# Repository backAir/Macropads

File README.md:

# Macropads

## 10x10 Macropad

[10x10 macropad](10x10/README.md)

## 4x3 Cuty Pad

[4x3 Cuty pad](<4x3 cuty pad/README.md>)

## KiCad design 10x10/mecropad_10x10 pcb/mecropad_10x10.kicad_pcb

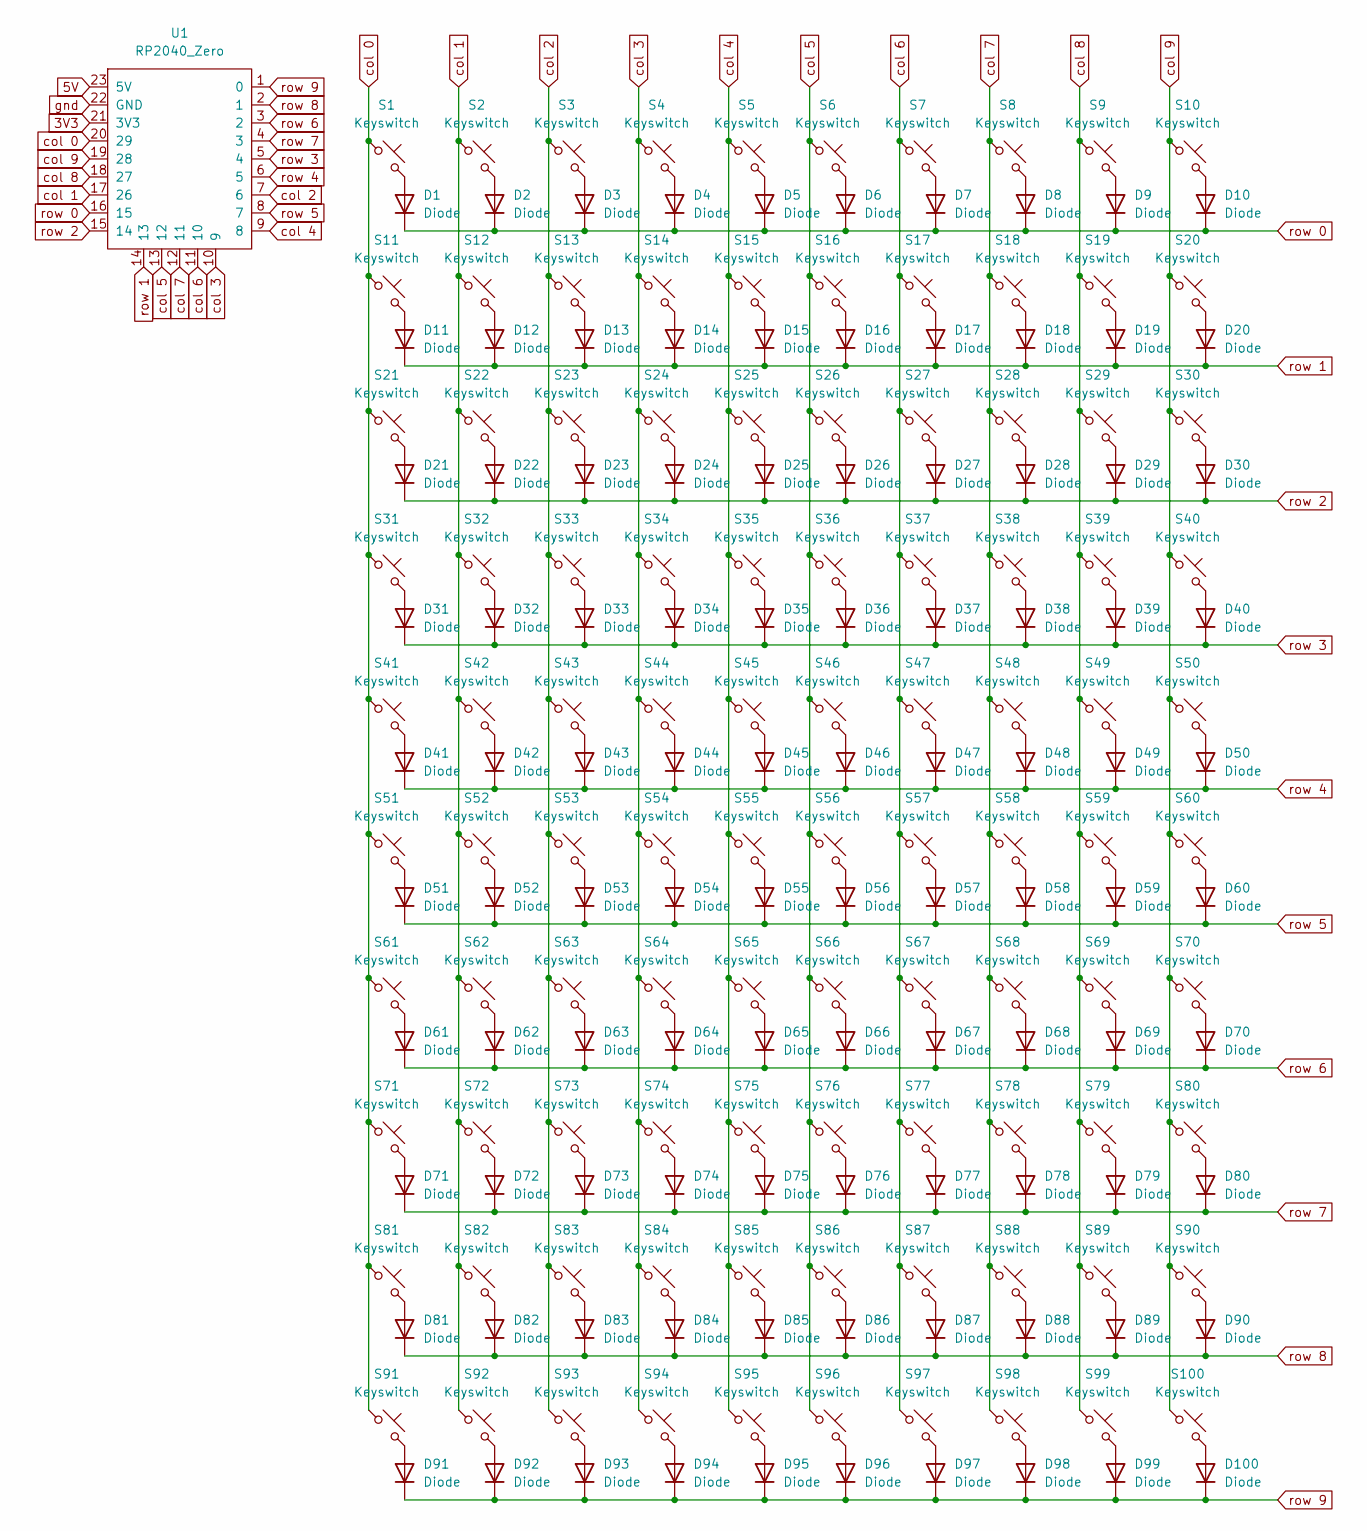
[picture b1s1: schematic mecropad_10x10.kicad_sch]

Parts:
D1, D2, D3, D4, D5, D6, D7, D8, D9, D10, D11, D12, D13, D14, D15, D16, D17, D18, D19, D20, D21, D22, D23, D24, D25, D26, D27, D28, D29, D30, D31, D32, D33, D34, D35, D36, D37, D38, D39, D40, D41, D42, D43, D44, D45, D46, D47, D48, D49, D50, D51, D52, D53, D54, D55, D56, D57, D58, D59, D60, D61, D62, D63, D64, D65, D66, D67, D68, D69, D70, D71, D72, D73, D74, D75, D76, D77, D78, D79, D80, D81, D82, D83, D84, D85, D86, D87, D88, D89, D90, D91, D92, D93, D94, D95, D96, D97, D98, D99, D100: Diode; Diode_DO-35_smol
S1, S2, S3, S4, S5, S6, S7, S8, S9, S10, S11, S12, S13, S14, S15, S16, S17, S18, S19, S20, S21, S22, S23, S24, S25, S26, S27, S28, S29, S30, S31, S32, S33, S34, S35, S36, S37, S38, S39, S40, S41, S42, S43, S44, S45, S46, S47, S48, S49, S50, S51, S52, S53, S54, S55, S56, S57, S58, S59, S60, S61, S62, S63, S64, S65, S66, S67, S68, S69, S70, S71, S72, S73, S74, S75, S76, S77, S78, S79, S80, S81, S82, S83, S84, S85, S86, S87, S88, S89, S90, S91, S92, S93, S94, S95, S96, S97, S98, S99, S100: Keyswitch; SW_BUTT-2
U1: RP2040_Zero; RP2040_Zero_round_pads

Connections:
3V3: U1.21 (3V3)
5V: U1.23 (5V)
unnamed: D1.2 (A), S1.2
unnamed: D2.2 (A), S2.2
unnamed: D3.2 (A), S3.2
unnamed: D4.2 (A), S4.2
unnamed: D5.2 (A), S5.2
unnamed: D6.2 (A), S6.2
unnamed: D7.2 (A), S7.2
unnamed: D8.2 (A), S8.2
unnamed: D9.2 (A), S9.2
unnamed: D10.2 (A), S10.2
unnamed: D11.2 (A), S11.2
unnamed: D12.2 (A), S12.2
unnamed: D13.2 (A), S13.2
unnamed: D14.2 (A), S14.2
unnamed: D15.2 (A), S15.2
unnamed: D16.2 (A), S16.2
unnamed: D17.2 (A), S17.2
unnamed: D18.2 (A), S18.2
unnamed: D19.2 (A), S19.2
unnamed: D20.2 (A), S20.2
unnamed: D21.2 (A), S21.2
unnamed: D22.2 (A), S22.2
unnamed: D23.2 (A), S23.2
unnamed: D24.2 (A), S24.2
unnamed: D25.2 (A), S25.2
unnamed: D26.2 (A), S26.2
unnamed: D27.2 (A), S27.2
unnamed: D28.2 (A), S28.2
unnamed: D29.2 (A), S29.2
unnamed: D30.2 (A), S30.2
unnamed: D31.2 (A), S31.2
unnamed: D32.2 (A), S32.2
unnamed: D33.2 (A), S33.2
unnamed: D34.2 (A), S34.2
unnamed: D35.2 (A), S35.2
unnamed: D36.2 (A), S36.2
unnamed: D37.2 (A), S37.2
unnamed: D38.2 (A), S38.2
unnamed: D39.2 (A), S39.2
unnamed: D40.2 (A), S40.2
unnamed: D41.2 (A), S41.2
unnamed: D42.2 (A), S42.2
unnamed: D43.2 (A), S43.2
unnamed: D44.2 (A), S44.2
unnamed: D45.2 (A), S45.2
unnamed: D46.2 (A), S46.2
unnamed: D47.2 (A), S47.2
unnamed: D48.2 (A), S48.2
unnamed: D49.2 (A), S49.2
unnamed: D50.2 (A), S50.2
unnamed: D51.2 (A), S51.2
unnamed: D52.2 (A), S52.2
unnamed: D53.2 (A), S53.2
unnamed: D54.2 (A), S54.2
unnamed: D55.2 (A), S55.2
unnamed: D56.2 (A), S56.2
unnamed: D57.2 (A), S57.2
unnamed: D58.2 (A), S58.2
unnamed: D59.2 (A), S59.2
unnamed: D60.2 (A), S60.2
unnamed: D61.2 (A), S61.2
unnamed: D62.2 (A), S62.2
unnamed: D63.2 (A), S63.2
unnamed: D64.2 (A), S64.2
unnamed: D65.2 (A), S65.2
unnamed: D66.2 (A), S66.2
unnamed: D67.2 (A), S67.2
unnamed: D68.2 (A), S68.2
unnamed: D69.2 (A), S69.2
unnamed: D70.2 (A), S70.2
unnamed: D71.2 (A), S71.2
unnamed: D72.2 (A), S72.2
unnamed: D73.2 (A), S73.2
unnamed: D74.2 (A), S74.2
unnamed: D75.2 (A), S75.2
unnamed: D76.2 (A), S76.2
unnamed: D77.2 (A), S77.2
unnamed: D78.2 (A), S78.2
unnamed: D79.2 (A), S79.2
unnamed: D80.2 (A), S80.2
unnamed: D81.2 (A), S81.2
unnamed: D82.2 (A), S82.2
unnamed: D83.2 (A), S83.2
unnamed: D84.2 (A), S84.2
unnamed: D85.2 (A), S85.2
unnamed: D86.2 (A), S86.2
unnamed: D87.2 (A), S87.2
unnamed: D88.2 (A), S88.2
unnamed: D89.2 (A), S89.2
unnamed: D90.2 (A), S90.2
unnamed: D91.2 (A), S91.2
unnamed: D92.2 (A), S92.2
unnamed: D93.2 (A), S93.2
unnamed: D94.2 (A), S94.2
unnamed: D95.2 (A), S95.2
unnamed: D96.2 (A), S96.2
unnamed: D97.2 (A), S97.2
unnamed: D98.2 (A), S98.2
unnamed: D99.2 (A), S99.2
unnamed: D100.2 (A), S100.2
col 0: S1.1, S11.1, S21.1, S31.1, S41.1, S51.1, S61.1, S71.1, S81.1, S91.1, U1.20 (29)
col 1: S2.1, S12.1, S22.1, S32.1, S42.1, S52.1, S62.1, S72.1, S82.1, S92.1, U1.17 (26)
col 2: S3.1, S13.1, S23.1, S33.1, S43.1, S53.1, S63.1, S73.1, S83.1, S93.1, U1.7 (6)
col 3: S4.1, S14.1, S24.1, S34.1, S44.1, S54.1, S64.1, S74.1, S84.1, S94.1, U1.10 (9)
col 4: S5.1, S15.1, S25.1, S35.1, S45.1, S55.1, S65.1, S75.1, S85.1, S95.1, U1.9 (8)
col 5: S6.1, S16.1, S26.1, S36.1, S46.1, S56.1, S66.1, S76.1, S86.1, S96.1, U1.13 (12)
col 6: S7.1, S17.1, S27.1, S37.1, S47.1, S57.1, S67.1, S77.1, S87.1, S97.1, U1.11 (10)
col 7: S8.1, S18.1, S28.1, S38.1, S48.1, S58.1, S68.1, S78.1, S88.1, S98.1, U1.12 (11)
col 8: S9.1, S19.1, S29.1, S39.1, S49.1, S59.1, S69.1, S79.1, S89.1, S99.1, U1.18 (27)
col 9: S10.1, S20.1, S30.1, S40.1, S50.1, S60.1, S70.1, S80.1, S90.1, S100.1, U1.19 (28)
gnd: U1.22 (GND)
row 0: D1.1 (K), D2.1 (K), D3.1 (K), D4.1 (K), D5.1 (K), D6.1 (K), D7.1 (K), D8.1 (K), D9.1 (K), D10.1 (K), U1.16 (15)
row 1: D11.1 (K), D12.1 (K), D13.1 (K), D14.1 (K), D15.1 (K), D16.1 (K), D17.1 (K), D18.1 (K), D19.1 (K), D20.1 (K), U1.14 (13)
row 2: D21.1 (K), D22.1 (K), D23.1 (K), D24.1 (K), D25.1 (K), D26.1 (K), D27.1 (K), D28.1 (K), D29.1 (K), D30.1 (K), U1.15 (14)
row 3: D31.1 (K), D32.1 (K), D33.1 (K), D34.1 (K), D35.1 (K), D36.1 (K), D37.1 (K), D38.1 (K), D39.1 (K), D40.1 (K), U1.5 (4)
row 4: D41.1 (K), D42.1 (K), D43.1 (K), D44.1 (K), D45.1 (K), D46.1 (K), D47.1 (K), D48.1 (K), D49.1 (K), D50.1 (K), U1.6 (5)
row 5: D51.1 (K), D52.1 (K), D53.1 (K), D54.1 (K), D55.1 (K), D56.1 (K), D57.1 (K), D58.1 (K), D59.1 (K), D60.1 (K), U1.8 (7)
row 6: D61.1 (K), D62.1 (K), D63.1 (K), D64.1 (K), D65.1 (K), D66.1 (K), D67.1 (K), D68.1 (K), D69.1 (K), D70.1 (K), U1.3 (2)
row 7: D71.1 (K), D72.1 (K), D73.1 (K), D74.1 (K), D75.1 (K), D76.1 (K), D77.1 (K), D78.1 (K), D79.1 (K), D80.1 (K), U1.4 (3)
row 8: D81.1 (K), D82.1 (K), D83.1 (K), D84.1 (K), D85.1 (K), D86.1 (K), D87.1 (K), D88.1 (K), D89.1 (K), D90.1 (K), U1.2 (1)
row 9: D91.1 (K), D92.1 (K), D93.1 (K), D94.1 (K), D95.1 (K), D96.1 (K), D97.1 (K), D98.1 (K), D99.1 (K), D100.1 (K), U1.1 (0)

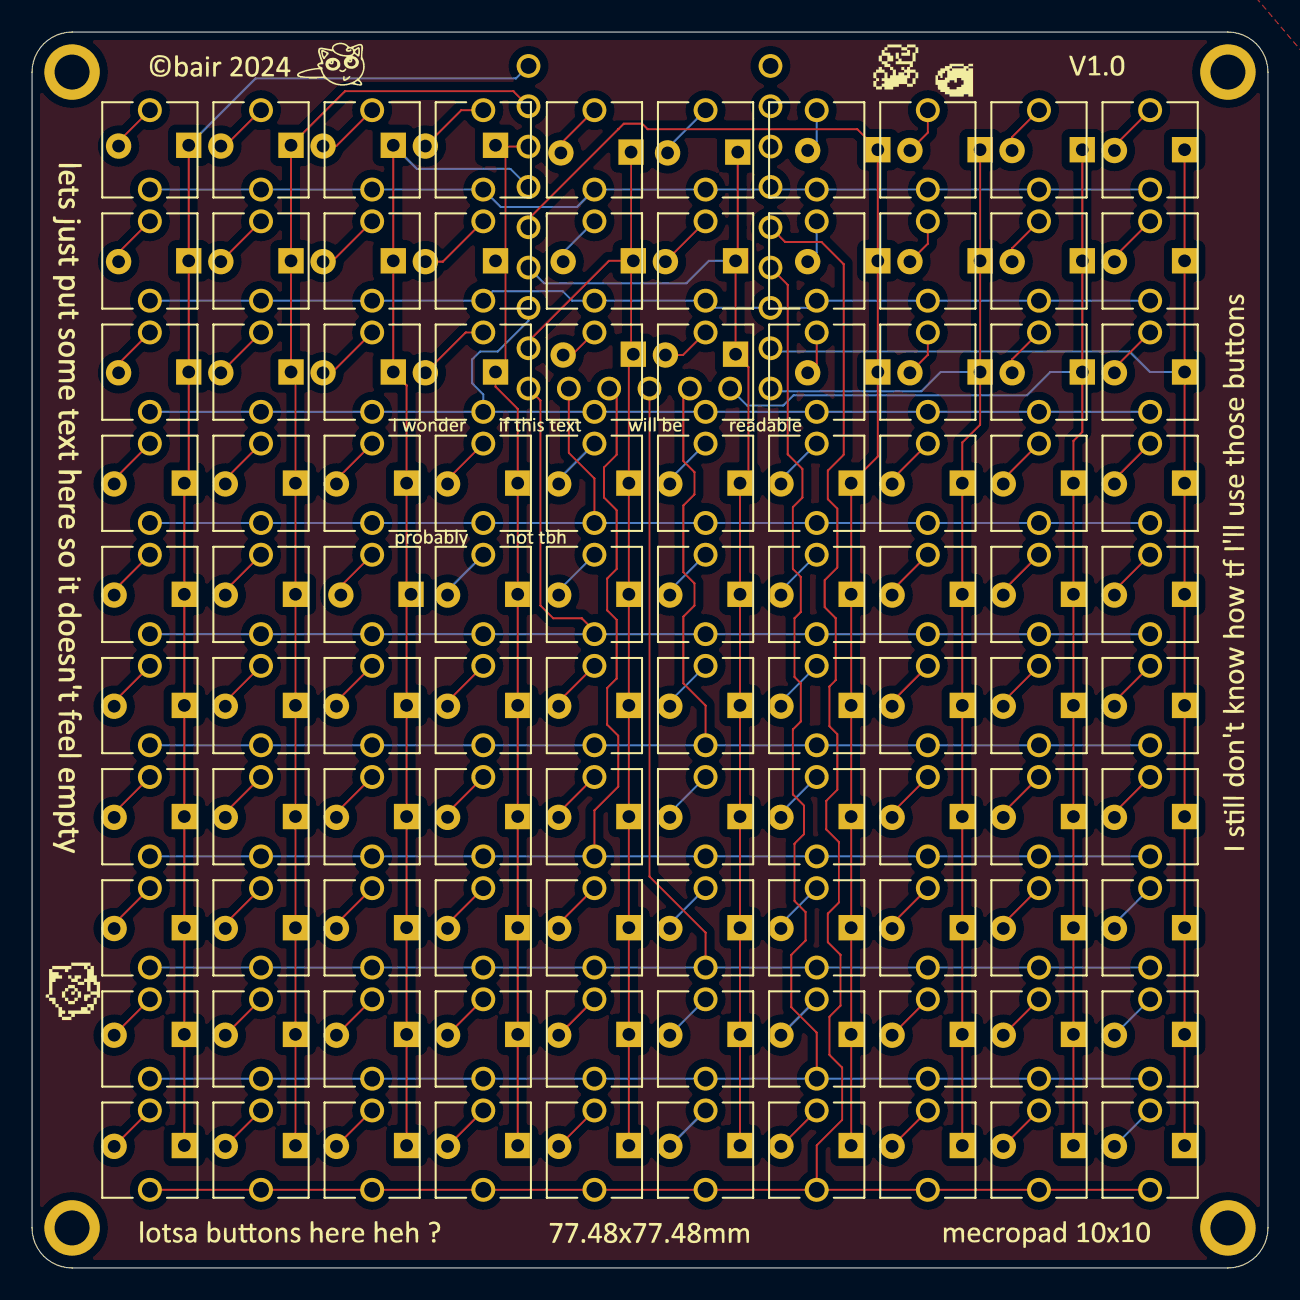
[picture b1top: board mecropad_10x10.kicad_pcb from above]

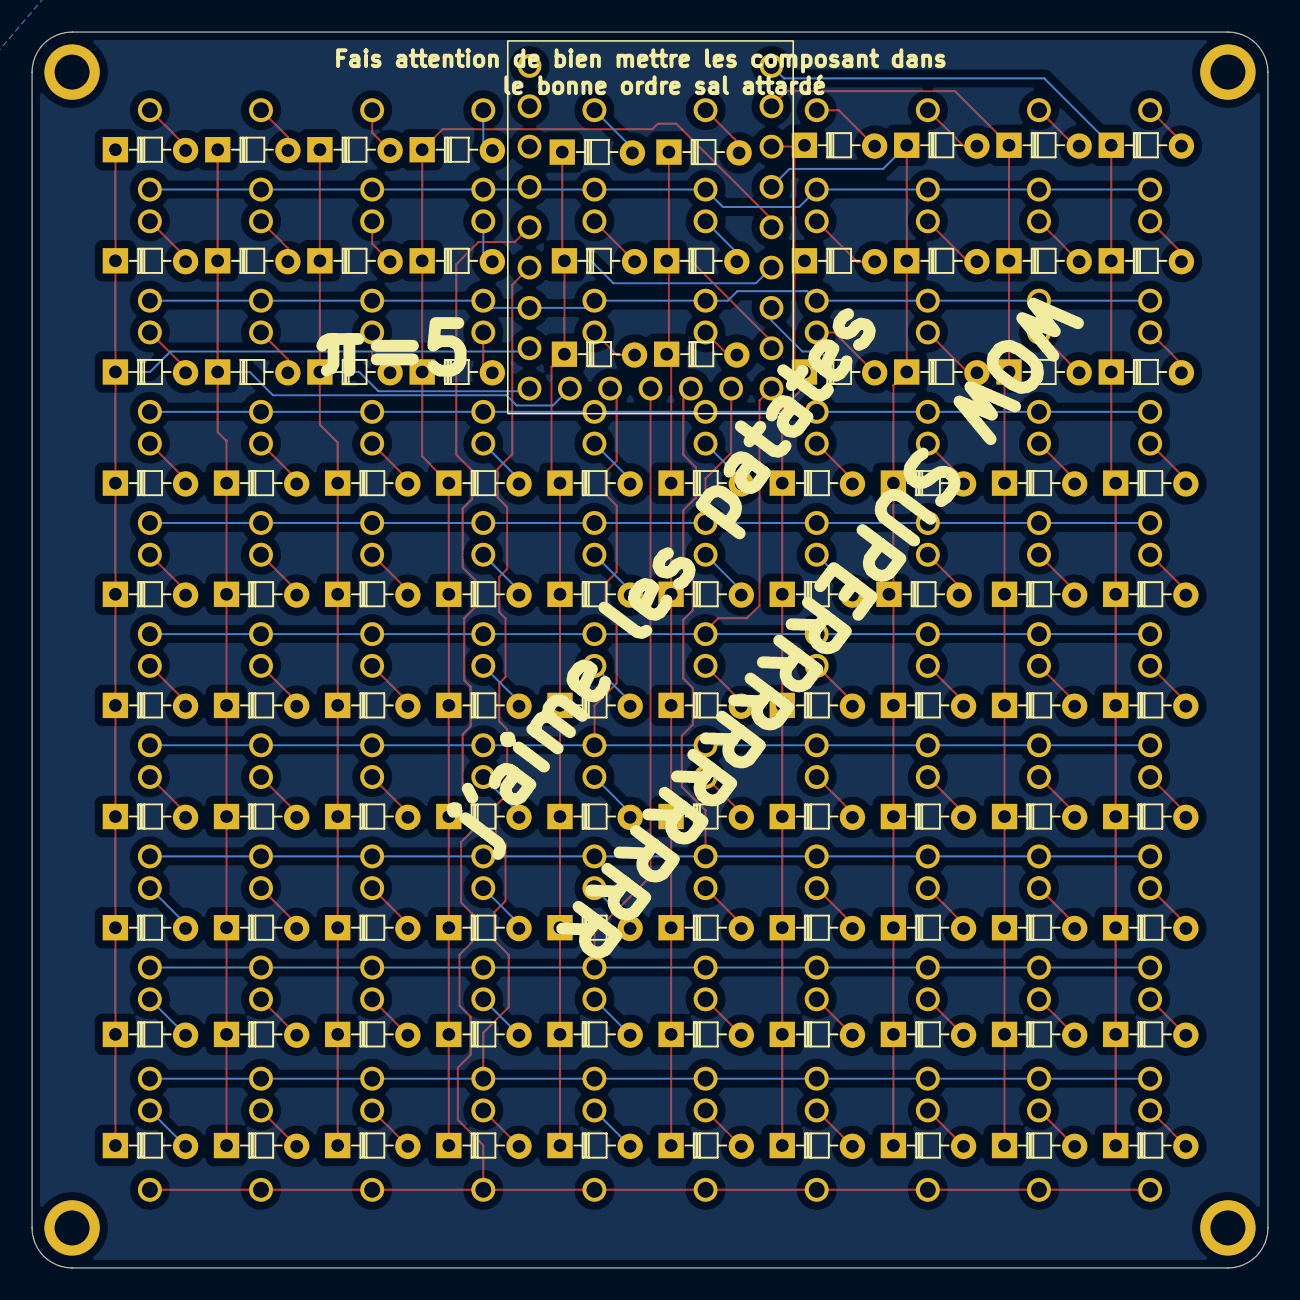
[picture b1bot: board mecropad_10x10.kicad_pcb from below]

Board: 2 copper layers, 77.8 x 77.8 mm, 201 parts (100 on the bottom side), 120 nets.

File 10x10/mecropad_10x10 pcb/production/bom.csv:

Designator,Footprint,Quantity,Value,LCSC Part #
"D1, D10, D100, D11, D12, D13, D14, D15, D16, D17, D18, D19, D2, D20, D21, D22, D23, D24, D25, D26, D27, D28, D29, D3, D30, D31, D32, D33, D34, D35, D36, D37, D38, D39, D4, D40, D41, D42, D43, D44, D45, D46, D47, D48, D49, D5, D50, D51, D52, D53, D54, D55, D56, D57, D58, D59, D6, D60, D61, D62, D63, D64, D65, D66, D67, D68, D69, D7, D70, D71, D72, D73, D74, D75, D76, D77, D78, D79, D8, D80, D81, D82, D83, D84, D85, D86, D87, D88, D89, D9, D90, D91, D92, D93, D94, D95, D96, D97, D98, D99",Diode_DO-35_smol,100,Diode,
"S1, S10, S100, S11, S12, S13, S14, S15, S16, S17, S18, S19, S2, S20, S21, S22, S23, S24, S25, S26, S27, S28, S29, S3, S30, S31, S32, S33, S34, S35, S36, S37, S38, S39, S4, S40, S41, S42, S43, S44, S45, S46, S47, S48, S49, S5, S50, S51, S52, S53, S54, S55, S56, S57, S58, S59, S6, S60, S61, S62, S63, S64, S65, S66, S67, S68, S69, S7, S70, S71, S72, S73, S74, S75, S76, S77, S78, S79, S8, S80, S81, S82, S83, S84, S85, S86, S87, S88, S89, S9, S90, S91, S92, S93, S94, S95, S96, S97, S98, S99",SW_BUTT-2,100,Keyswitch,
U1,RP2040_Zero_round_pads,1,RP2040_Zero,

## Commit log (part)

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2024-05-02 Added 3d models
2024-05-02 pcb files
2024-05-27 Update Readme + LICENSE
